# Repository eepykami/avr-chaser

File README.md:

# avr-chaser
Chaser light using ATTINY85, with example Makefile and VSCode setup.

## Build
Project is built using avr-gcc. Programmer used is USBasp.

Clone this repo, then:

```sh
make clean
make all
```

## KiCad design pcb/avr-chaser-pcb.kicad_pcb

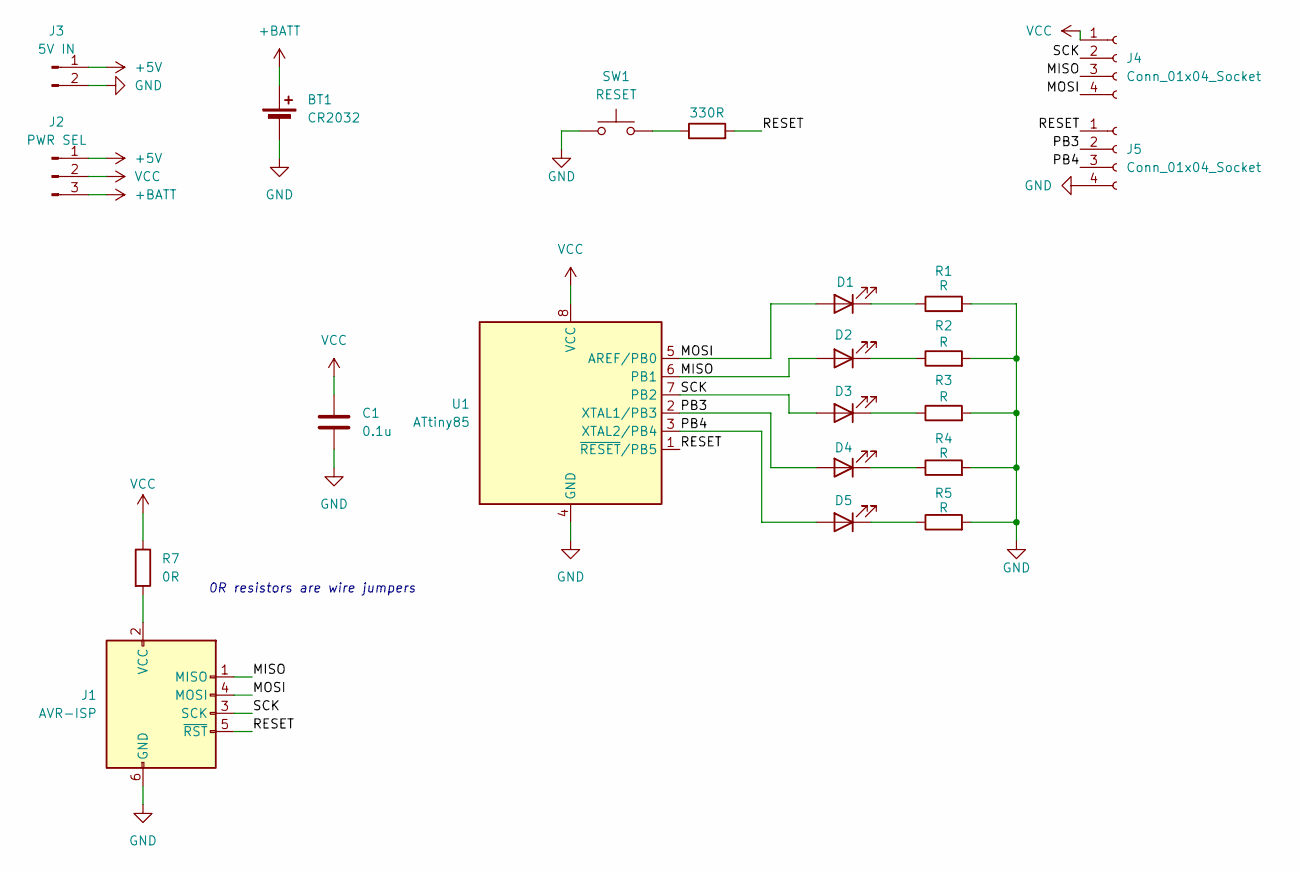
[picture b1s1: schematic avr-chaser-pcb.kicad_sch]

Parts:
BT1: CR2032; Battery_Panasonic_CR2032-HFN_Horizontal_CircularHoles
C1: 0.1u; C_Disc_D3.0mm_W1.6mm_P2.50mm
D1: PB0; LED_D5.0mm
D2: PB1; LED_D5.0mm
D3: PB2; LED_D5.0mm
D4: PB3; LED_D5.0mm
D5: PB4; LED_D5.0mm
J1: AVR-ISP; PinHeader_2x03_P2.54mm_Vertical
J2: PWR SEL; PinHeader_1x03_P2.54mm_Vertical
J3: 5V IN; PinHeader_1x02_P2.54mm_Vertical
J4, J5: Conn_01x04_Socket; PinSocket_1x04_P2.54mm_Vertical
R1, R2, R3, R4, R5: R; R_Axial_DIN0207_L6.3mm_D2.5mm_P10.16mm_Horizontal
R6: 330R; R_Axial_DIN0207_L6.3mm_D2.5mm_P10.16mm_Horizontal
R7: 0R; R_Axial_DIN0207_L6.3mm_D2.5mm_P15.24mm_Horizontal
SW1: RESET; SW_PUSH_6mm
U1: ATtiny85; DIP-8_W7.62mm_Socket_LongPads

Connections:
+5V: J2.1, J3.1
+BATT: BT1.1 (+), J2.3
/MISO: D2.2 (A), J1.1 (MISO), J4.3, U1.6 (PB1)
/MOSI: D1.2 (A), J1.4 (MOSI), J4.4, U1.5 (AREF/PB0)
/PB3: D4.2 (A), J5.2, U1.2 (XTAL1/PB3)
/PB4: D5.2 (A), J5.3, U1.3 (XTAL2/PB4)
/RESET: J1.5 (~RST), J5.1, R6.2, U1.1 (~RESET/PB5)
/SCK: D3.2 (A), J1.3 (SCK), J4.2, U1.7 (PB2)
GND: BT1.2 (-), C1.2, J1.6 (GND), J3.2, J5.4, R1.2, R2.2, R3.2, R4.2, R5.2, SW1.1, U1.4 (GND)
unnamed: D1.1 (K), R1.1
unnamed: D2.1 (K), R2.1
unnamed: D3.1 (K), R3.1
unnamed: D4.1 (K), R4.1
unnamed: D5.1 (K), R5.1
unnamed: J1.2 (VCC), R7.2
unnamed: R6.1, SW1.2
VCC: C1.1, J2.2, J4.1, R7.1, U1.8 (VCC)

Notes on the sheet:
0R resistors are wire jumpers

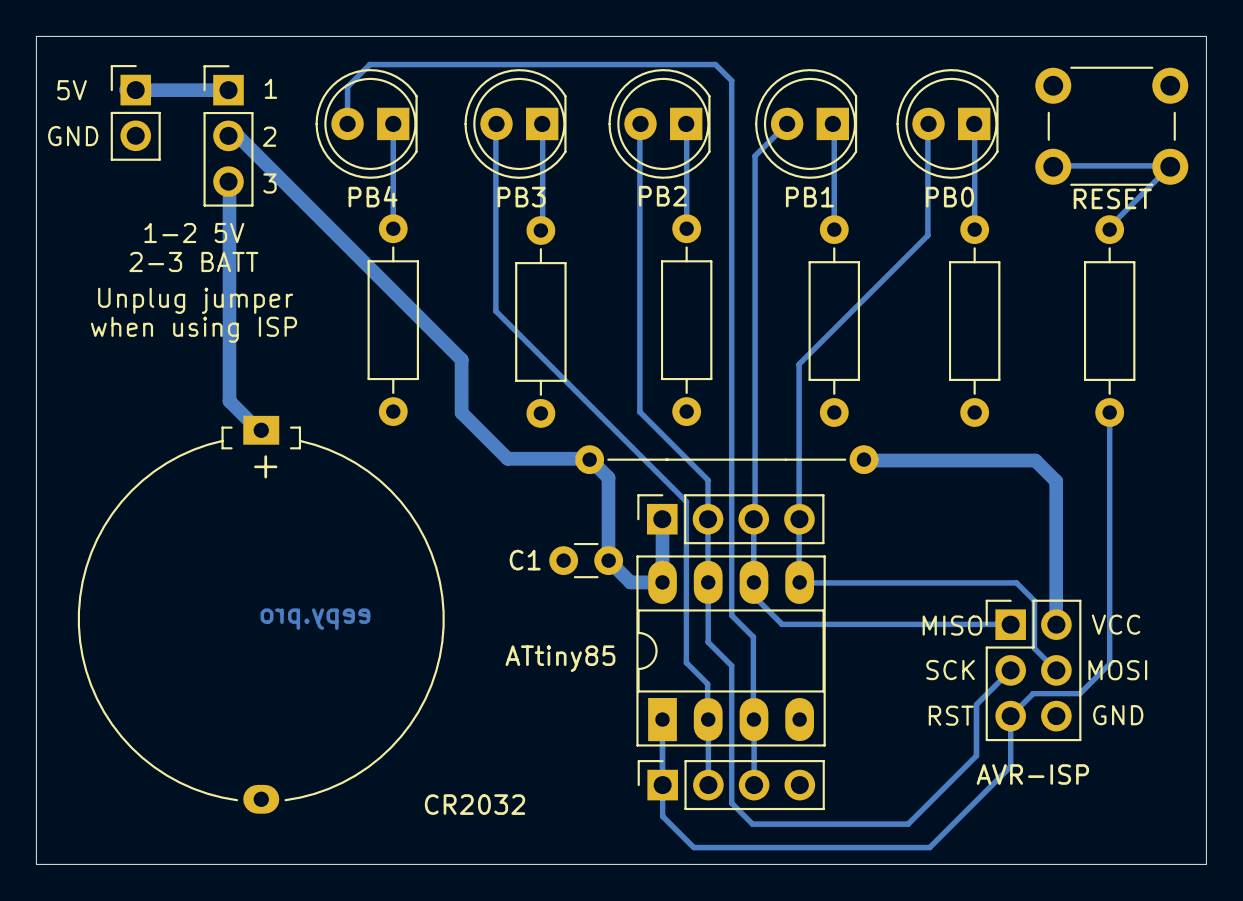
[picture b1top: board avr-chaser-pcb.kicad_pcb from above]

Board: 2 copper layers, 65.0 x 46.0 mm, 21 parts (0 on the bottom side), 17 nets.

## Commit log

2024-03-08 Create Makefile
2024-03-09 Add GIF and update README.md
2024-08-11 Add PCB
